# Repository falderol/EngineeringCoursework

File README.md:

This repository contains completed engineering related projects that have been completed while attending taylor university. 
The current order in which projects were completed is.

ENP 104

ENP 232

ENP 252

More projects are currently being worked on. They will be added upon completion.

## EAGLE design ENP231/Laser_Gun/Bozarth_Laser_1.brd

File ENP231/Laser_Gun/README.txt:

File has 3 boards, 1 is main, mode just contains a switch and trigger just contains a button

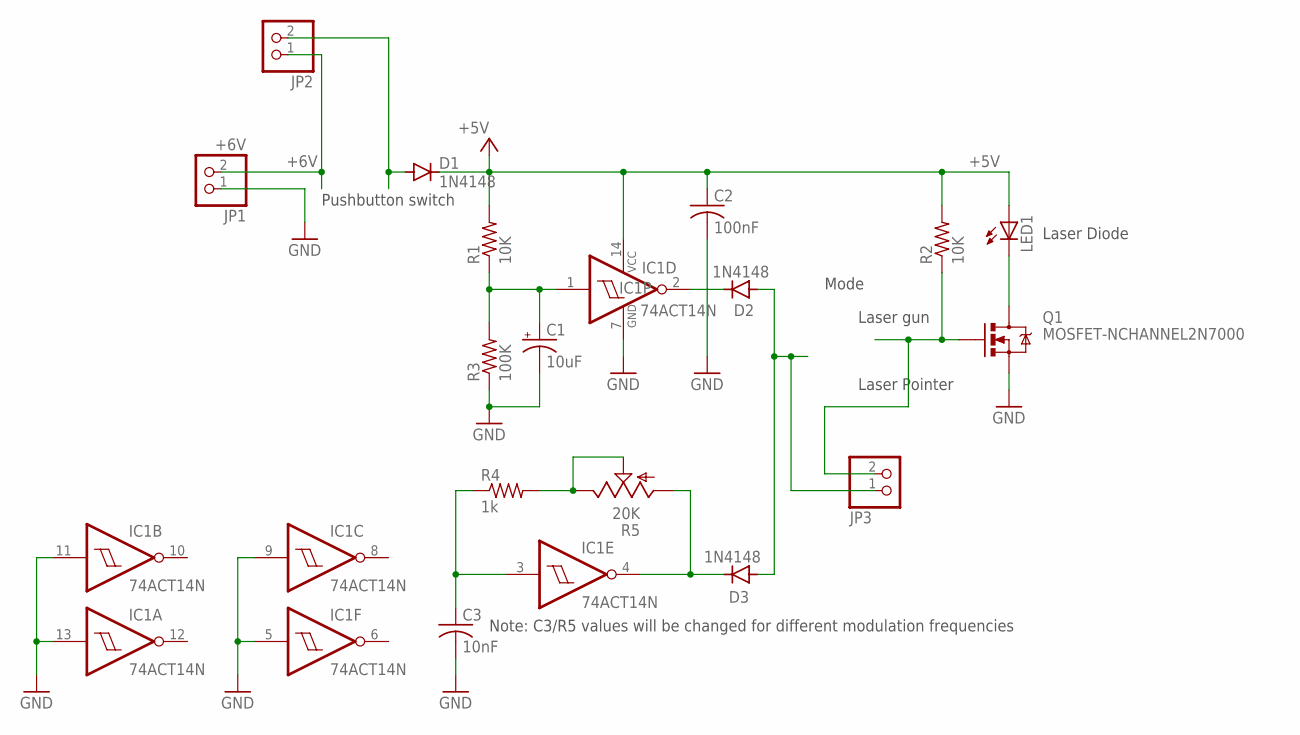
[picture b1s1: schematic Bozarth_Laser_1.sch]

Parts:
C1: 10uF; E2-5
C2: 100nF; C025-025X050
C3: 10nF; C025-025X050
D1, D2, D3: 1N4148; 0207/2V-D
IC1: 74ACT14N; DIL14
JP1: +6V; 1X02
JP2, JP3: PINHD-1X2; 1X02
LED1: LED5MM
Q1: MOSFET-NCHANNEL2N7000; TO-92
R1, R2: 10K; 0207/10
R3: 100K; 0207/10
R4: 1k; 0207/10
R5: 20K; B64Y

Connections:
+5V: C2.1, D1.K (C), IC1.14 (VCC), LED1.A, R1.2, R2.2
+6V: JP1.2, JP2.1
GND: C1.-, C2.2, C3.2, IC1.5 (I), IC1.7 (GND), IC1.9 (I), IC1.11 (I), IC1.13 (I), JP1.1, Q1.1 (S), R3.1
unnamed: C1.+, IC1.1 (I), R1.1, R3.2
unnamed: D2.A, D3.A, JP3.1
unnamed: LED1.K (C), Q1.3 (D)
unnamed: D1.A, JP2.2
unnamed: D2.K (C), IC1.2 (O)
unnamed: D3.K (C), IC1.4 (O), R5.A
unnamed: R4.2, R5.E, R5.S
unnamed: C3.1, IC1.3 (I), R4.1
unnamed: JP3.2, Q1.2 (G), R2.1

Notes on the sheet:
Pushbutton switch
Laser Pointer
Laser gun
Mode
Laser Diode
Note: C3/R5 values will be changed for different modulation frequencies

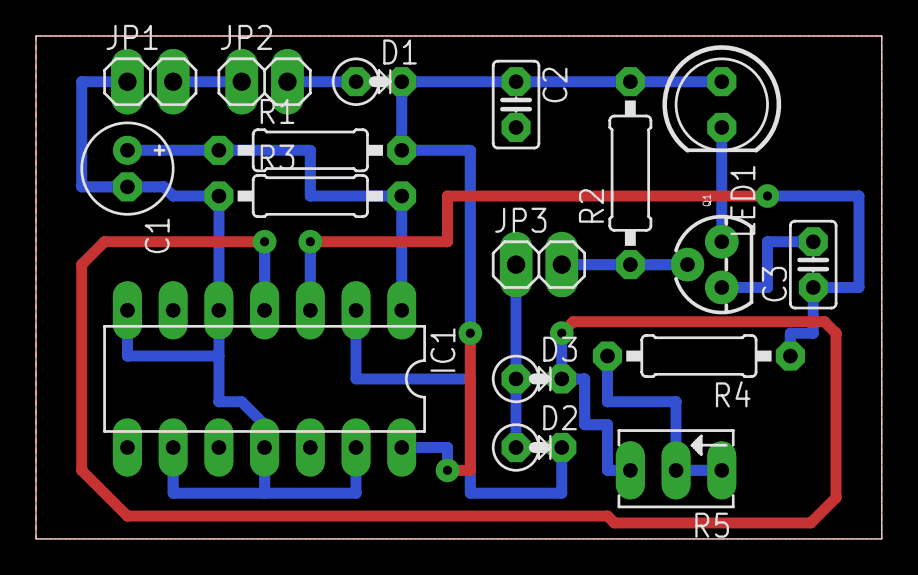
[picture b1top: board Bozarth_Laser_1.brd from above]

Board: 2 copper layers, 47.0 x 27.9 mm, 17 parts (0 on the bottom side), 12 nets.

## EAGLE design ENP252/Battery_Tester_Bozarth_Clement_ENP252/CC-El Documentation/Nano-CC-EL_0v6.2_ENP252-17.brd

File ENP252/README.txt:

Relevant coursework from ENP252 Principles of Engineering. Files included mainly relate to the construction of a programmable ellectronic current load with the class ran through an arduino. And the personal project of developing a battery tester application for said current load.

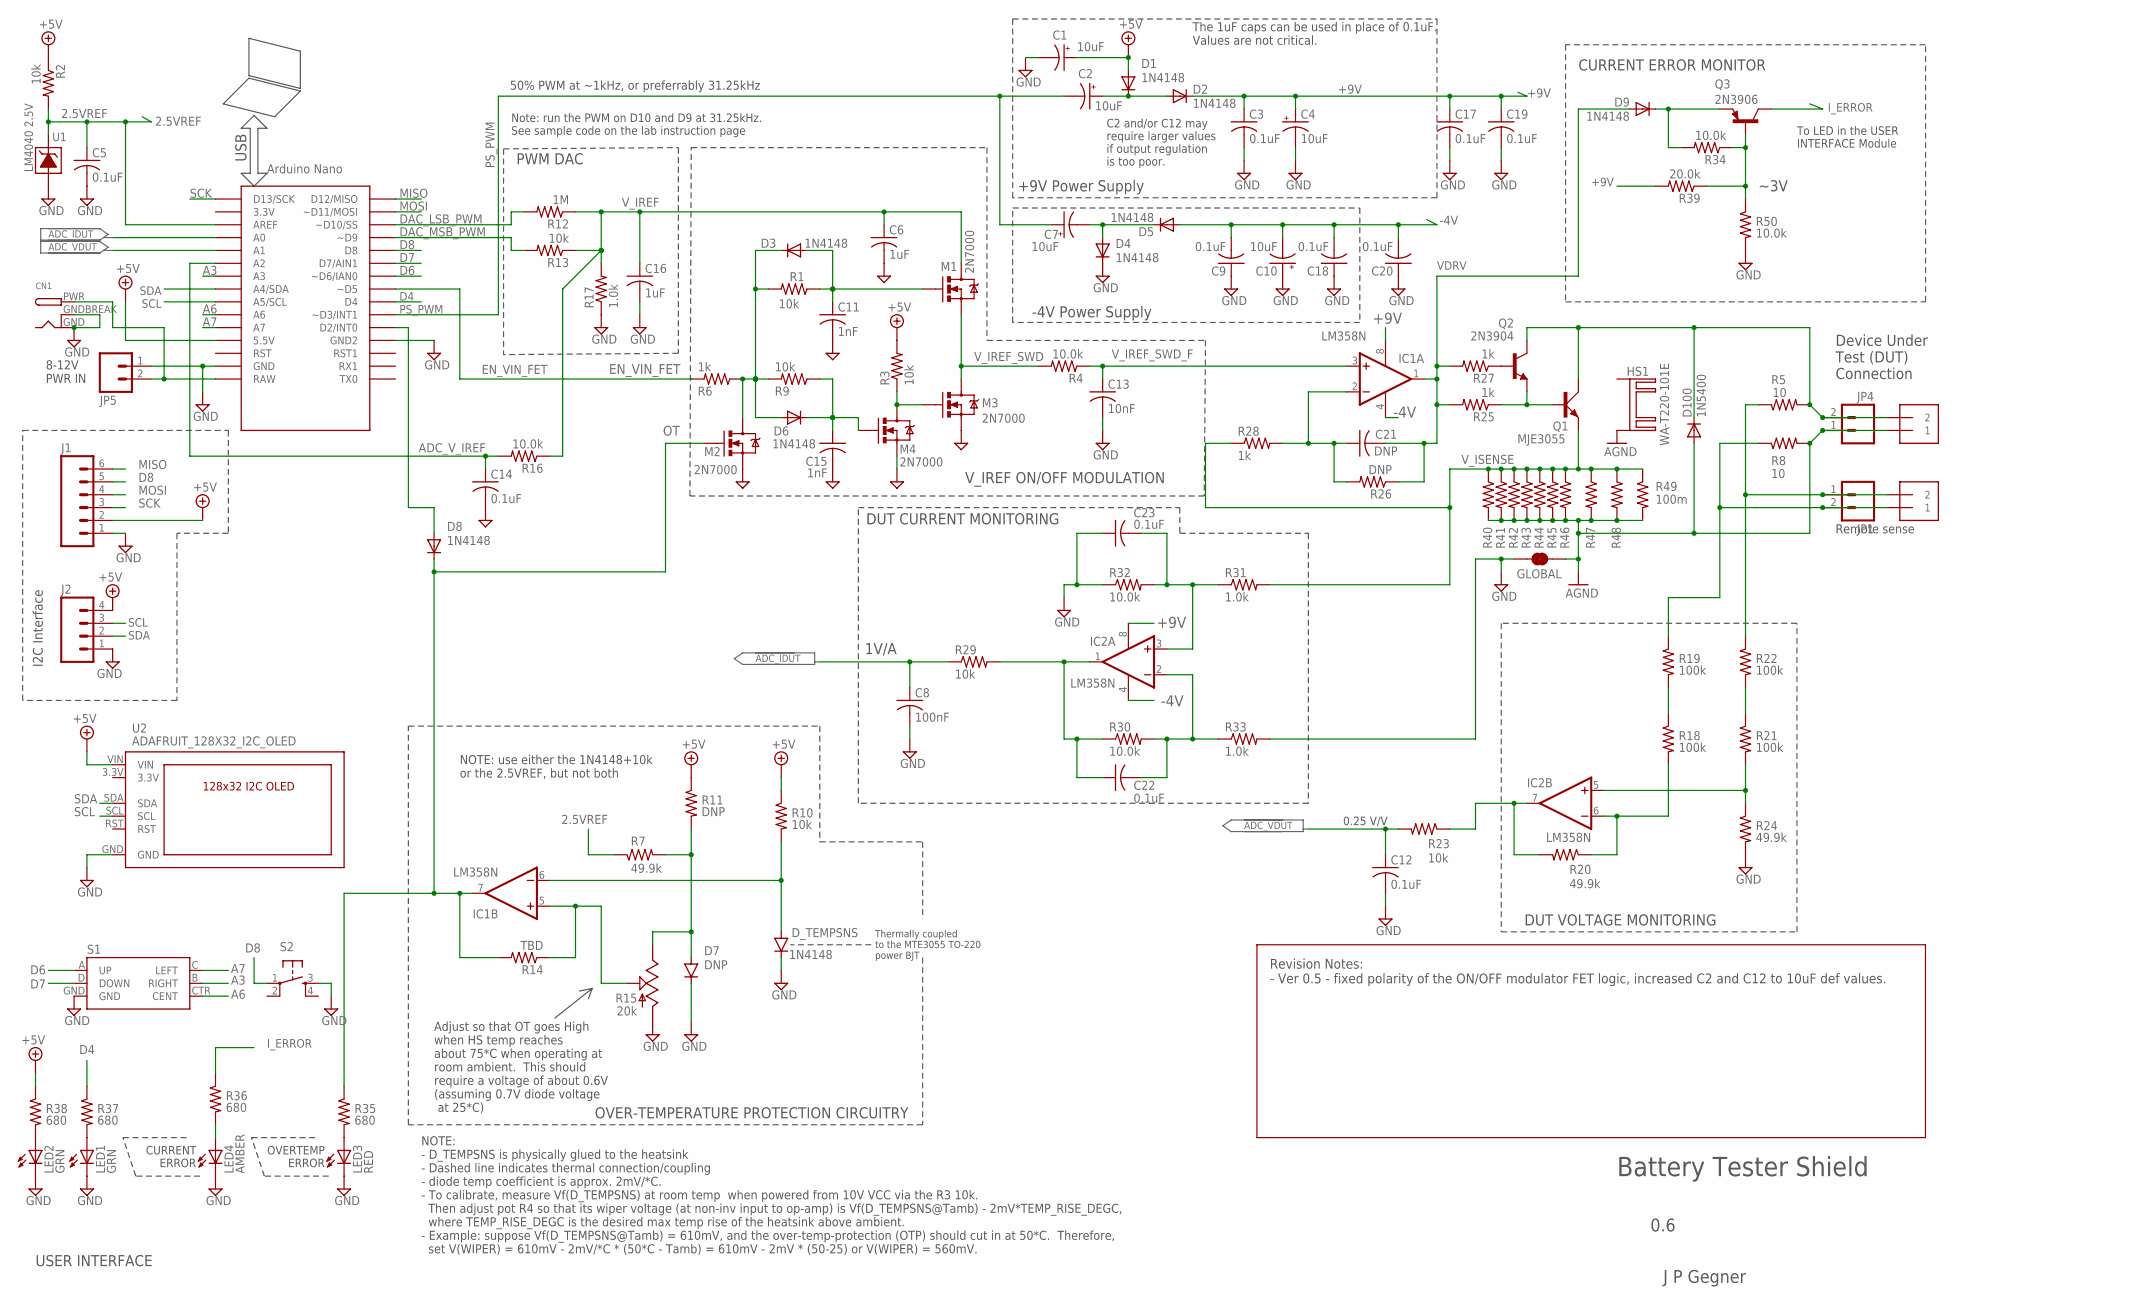
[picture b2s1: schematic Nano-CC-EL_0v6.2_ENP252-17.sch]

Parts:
C1, C2, C4, C7, C10: 10uF; E5-5
C3, C5, C9, C12, C14, C17, C18, C19, C20, C22, C23: 0.1uF; C025-025X050
C6, C16: 1uF; C025-025X050
C8: 100nF; C025-024X044
C11, C15: 1nF; C025-025X050
C13: 10nF; C025-025X050
C21: DNP; C025-025X050
CN1: DCBARRELPTH; DCJACK_2MM_PTH
D1, D2, D3, D4, D5, D6, D8, D9: 1N4148; 0207/2V-D
D7: DNP; 0207/2V-D
D100: 1N5400; DO201-15
D_TEMPSNS: 1N4148; 0207/2V-D
GLOBAL: JUMPER-PAD-2-NC_BY_TRACENO_SILK; PAD-JUMPER-2-NC_BY_TRACE_NO_SILK
HS1: WA-T220-101E; WX-T220-101E
IC1, IC2: LM358N; DIL08
J1: M06POLAR; MOLEX-1X6
J2: M04LOCK_LONGPADS; 1X04_LOCK_LONGPADS
JP1, JP4, JP5: M02PTH; 1X02
JP2, JP3: 1X2-3.5MM
LED1, LED2: GRN; LED3MM-NS
LED3: RED; LED3MM-NS
LED4: AMBER; LED3MM-NS
M1, M2, M3, M4: 2N7000; TO-92
Q1: MJE3055; TO220AV
Q2: 2N3904; TO92
Q3: 2N3906; TO92
R1, R2, R3, R9, R10, R13, R23, R29: 10k; 0204/7
R4, R30: 10.0k; 0204V
R5, R8: 10; 0204V
R6: 1k; 0204V
R7, R24: 49.9k; 0204/7
R11: DNP; 0204/7
R12: 1M; 0204/7
R14: TBD; 0204/7
R15: 20k; B64Y
R16, R32, R34, R50: 10.0k; 0204/7
R17, R31, R33: 1.0k; 0204/7
R18, R19, R21, R22: 100k; 0204/7
R20: 49.9k; 0204V
R25, R27, R28: 1k; 0204/7
R26: DNP; 0204V
R35, R36, R38: 680; 0204/7
R37: 680; 0207/15
R39: 20.0k; 0204/7
R40, R41, R42, R43, R44, R45, R46, R47, R48, R49: 100m; 0204/7
S1: JOYSTICK_MINI
S2: E-SWITCH_TL1105L-F250-Q; OMRON_B3F-1XX-JPGMOD
U1: LM4040 2.5V; TO92
U2: ADAFRUIT_128X32_I2C_OLED
U$1: NANO

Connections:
2.5VREF: C5.1, R2.2, R7.1, U1.2 (CATHODE), U$1.AREF
3.3V: U2.3.3V
+5V: C1.+, D1.A, J1.2, J2.4, R2.1, R3.2, R10.1, R11.1, R38.1, U2.VIN, U$1.5V (5.5V)
+9V: C3.1, C4.+, C17.1, C19.1, D2.K (C), IC1.8 (V+), IC2.8 (V+), R39.2
-4V: C9.2, C10.-, C18.2, C20.2, D5.A, IC1.4 (V-), IC2.4 (V-)
A3: S1.B (RIGHT), U$1.A3
A6: S1.CTR (CENT), U$1.A6
A7: S1.C (LEFT), U$1.A7
ADC_IDUT: C8.1, R29.1, U$1.A0
ADC_VDUT: C12.1, R23.2, U$1.A1
ADC_V_IREF: C14.1, R16.2, U$1.A2
AGND: D100.A, GLOBAL.2, HS1.K2, JP3.1, JP4.1, R8.2, R40.2, R41.2, R42.2, R43.2, R44.2, R45.2, R46.2, R47.2, R48.2, R49.2
D4: R37.1, U$1.D4
D6: S1.A (UP), U$1.D6 (~D6/IAN0)
D7: S1.D (DOWN), U$1.D7 (D7/AIN1)
D8: J1.5, S2.1, U$1.D8
DAC_LSB_PWM: R12.2, U$1.D10 (~D10/SS)
DAC_MSB_PWM: R13.2, U$1.D9 (~D9)
EN_VIN_FET: R6.2, U$1.D5 (~D5)
EN_VIN_FETX: D3.K (C), D6.A, M2.3 (D), R1.2, R6.1, R9.2
GND: C1.-, C3.2, C4.-, C5.2, C6.2, C8.2, C9.1, C10.+, C11.2, C12.2, C13.2, C14.2, C15.2, C16.2, C17.2, C18.1, C19.2, C20.1, C23.1, CN1.GND, CN1.GNDBREAK, D4.K (C), D7.K (C), D_TEMPSNS.K (C), GLOBAL.1, J1.1, J2.1, JP5.1, LED1.K (C), LED2.K (C), LED3.K (C), LED4.K (C), M2.1 (S), M3.1 (S), M4.1 (S), R15.A, R17.1, R24.2, R32.1, R33.2, R50.2, S1.GND, S2.3 (S), U1.3 (ANODE), U2.GND, U$1.GND, U$1.GND1 (GND2)
I_ERROR: Q3.1 (C), R36.1
MISO: J1.6, U$1.D12 (D12/MISO)
MOSI: J1.4, U$1.D11 (~D11/MOSI)
unnamed: D7.A, R7.2, R11.2, R15.E
unnamed: R21.1, R22.2
unnamed: C23.2, IC2.3 (+IN), R31.1, R32.2
unnamed: C22.2, IC2.2 (-IN), R30.2, R33.1
unnamed: D_TEMPSNS.A, IC1.6 (-IN), R10.2
unnamed: IC1.5 (+IN), R14.1, R15.S
unnamed: C11.1, D3.A, M1.2 (G), R1.1
unnamed: D9.K (C), Q3.3 (E), R34.2
unnamed: IC2.6 (-IN), R18.2, R20.1
unnamed: C7.-, D4.A, D5.K (C)
unnamed: LED3.A, R35.2
unnamed: LED2.A, R38.2
unnamed: LED1.A, R37.2
unnamed: C22.1, IC2.1 (OUT), R29.2, R30.1
unnamed: LED4.A, R36.2
unnamed: Q3.2 (B), R34.1, R39.1, R50.1
unnamed: C2.+, D1.K (C), D2.A
unnamed: IC2.5 (+IN), R21.2, R24.1
unnamed: C15.1, D6.K (C), M4.2 (G), R9.1
unnamed: M3.2 (G), M4.3 (D), R3.1
unnamed: JP1.1, JP2.2, R5.1, R22.1
unnamed: D8.A, U$1.D2 (D2/INT0)
unnamed: Q2.2 (B), R27.1
unnamed: D100.C, JP3.2, JP4.2, Q1.C, Q2.1 (C), R5.2
unnamed: Q1.B, Q2.3 (E), R25.1
unnamed: R18.1, R19.2
unnamed: C21.1, IC1.2 (-IN), R26.2, R28.2
unnamed: JP1.2, JP2.1, R8.1, R19.1
OT: D8.K (C), IC1.7 (OUT), M2.2 (G), R14.2, R35.1
PS_PWM: C2.-, C7.+, U$1.D3 (~D3/INT1)
RAW: CN1.PWR, JP5.2, U$1.RAW
SCK: J1.3, U$1.D13 (D13/SCK)
SCL: J2.3, U2.SCL, U$1.A5 (A5/SCL)
SDA: J2.2, U2.SDA, U$1.A4 (A4/SDA)
VDRV: C21.2, D9.A, IC1.1 (OUT), R25.2, R26.1, R27.2
VDUT_OP: IC2.7 (OUT), R20.2, R23.1
V_IREF: C6.1, C16.1, M1.3 (D), R12.1, R13.1, R16.1, R17.2
V_IREF_SWD: M1.1 (S), M3.3 (D), R4.2
V_IREF_SWD_F: C13.1, IC1.3 (+IN), R4.1
V_ISENSE: Q1.E, R28.1, R31.2, R40.1, R41.1, R42.1, R43.1, R44.1, R45.1, R46.1, R47.1, R48.1, R49.1

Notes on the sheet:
Battery Tester Shield
0.6
J P Gegner
NOTE: - D_TEMPSNS is physically glued to the heatsink - Dashed line indicates thermal connection/coupling - diode temp coefficient is approx. 2mV/*C. - To calibrate, measure Vf(D_TEMPSNS) at room temp when powered from 10V VCC via the R3 10k. Then adjust pot R4 so that its wiper voltage (at non-inv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
Adjust so that OT goes High when HS temp reaches about 75*C when operating at room ambient. This should require a voltage of about 0.6V (assuming 0.7V diode voltage at 25*C)
OVER-TEMPERATURE PROTECTION CIRCUITRY
Thermally coupled to the MTE3055 TO-220 power BJT
The 1uF caps can be used in place of 0.1uF. Values are not critical.
8-12V PWR IN
50% PWM at ~1kHz, or preferrably 31.25kHz
+9V Power Supply
-4V Power Supply
Device Under Test (DUT) Connection
PWM DAC
V_IREF ON/OFF MODULATION
DUT CURRENT MONITORING
DUT VOLTAGE MONITORING
USER INTERFACE
USB
1V/A
Note: run the PWM on D10 and D9 at 31.25kHz. See sample code on the lab instruction page
0.25 V/V
CURRENT ERROR
OVERTEMP ERROR
To LED in the USER INTERFACE Module
CURRENT ERROR MONITOR
~3V
I2C Interface
C2 and/or C12 may require larger values if output regulation is too poor.
Revision Notes: - Ver 0.5 - fixed polarity of the ON/OFF modulator FET logic, increased C2 and C12 to 10uF def values.
Remote sense
NOTE: use either the 1N4148+10k or the 2.5VREF, but not both

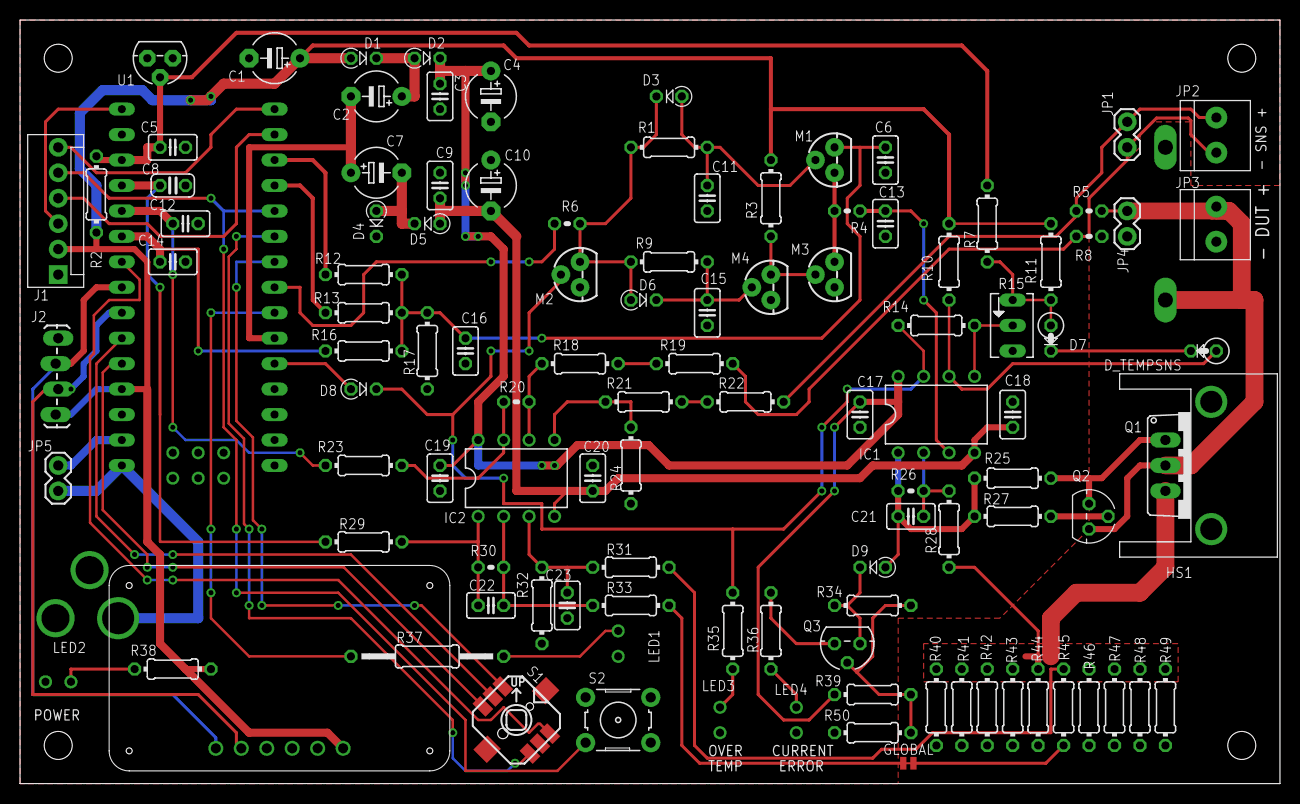
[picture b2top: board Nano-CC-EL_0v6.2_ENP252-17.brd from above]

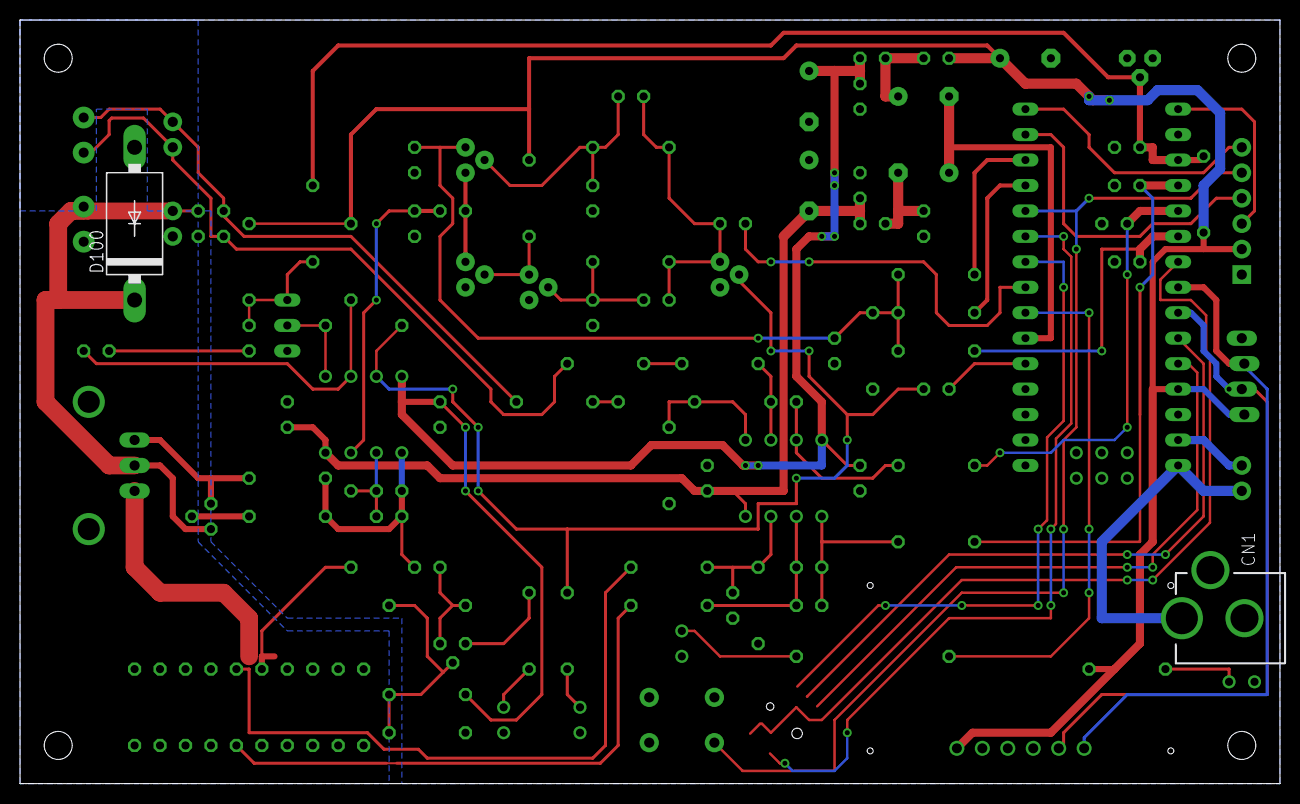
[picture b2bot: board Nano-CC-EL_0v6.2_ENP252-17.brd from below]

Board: 2 copper layers, 125.7 x 76.2 mm, 112 parts (2 on the bottom side), 63 nets.

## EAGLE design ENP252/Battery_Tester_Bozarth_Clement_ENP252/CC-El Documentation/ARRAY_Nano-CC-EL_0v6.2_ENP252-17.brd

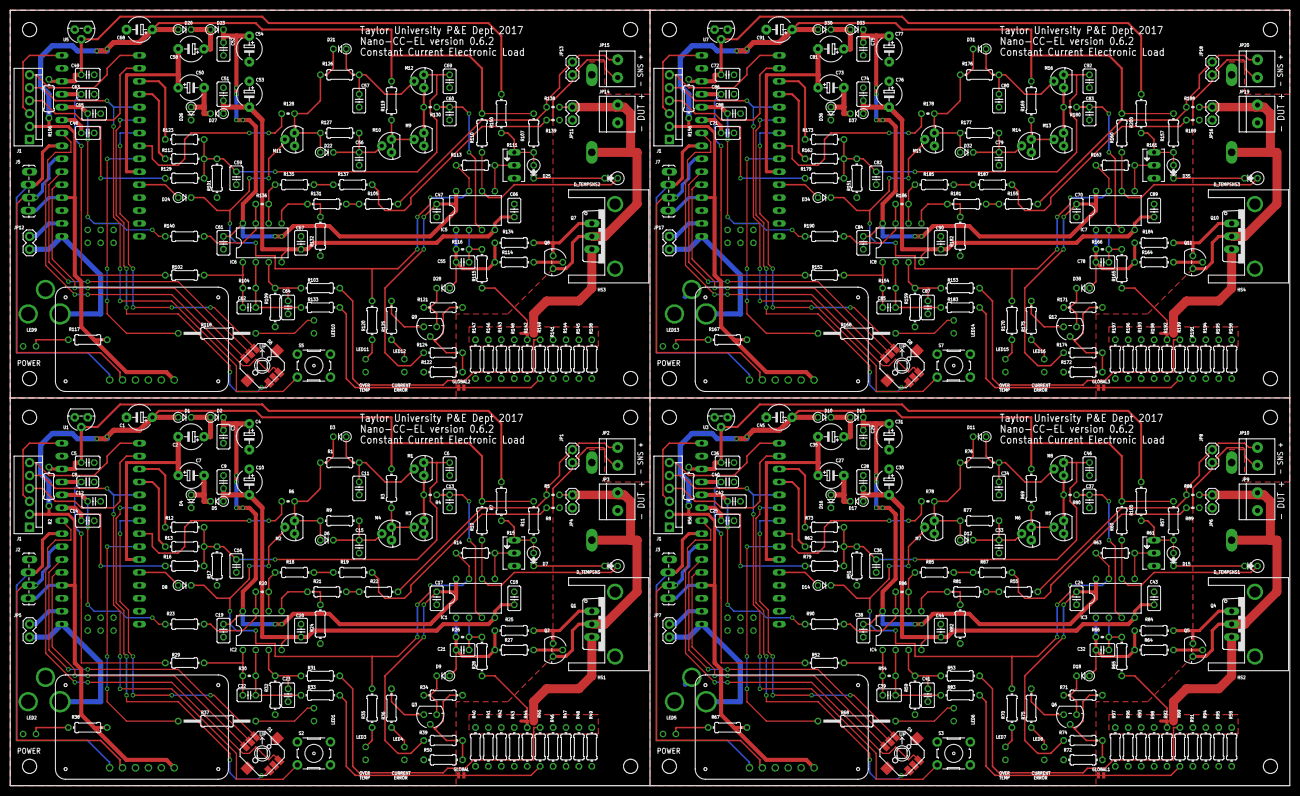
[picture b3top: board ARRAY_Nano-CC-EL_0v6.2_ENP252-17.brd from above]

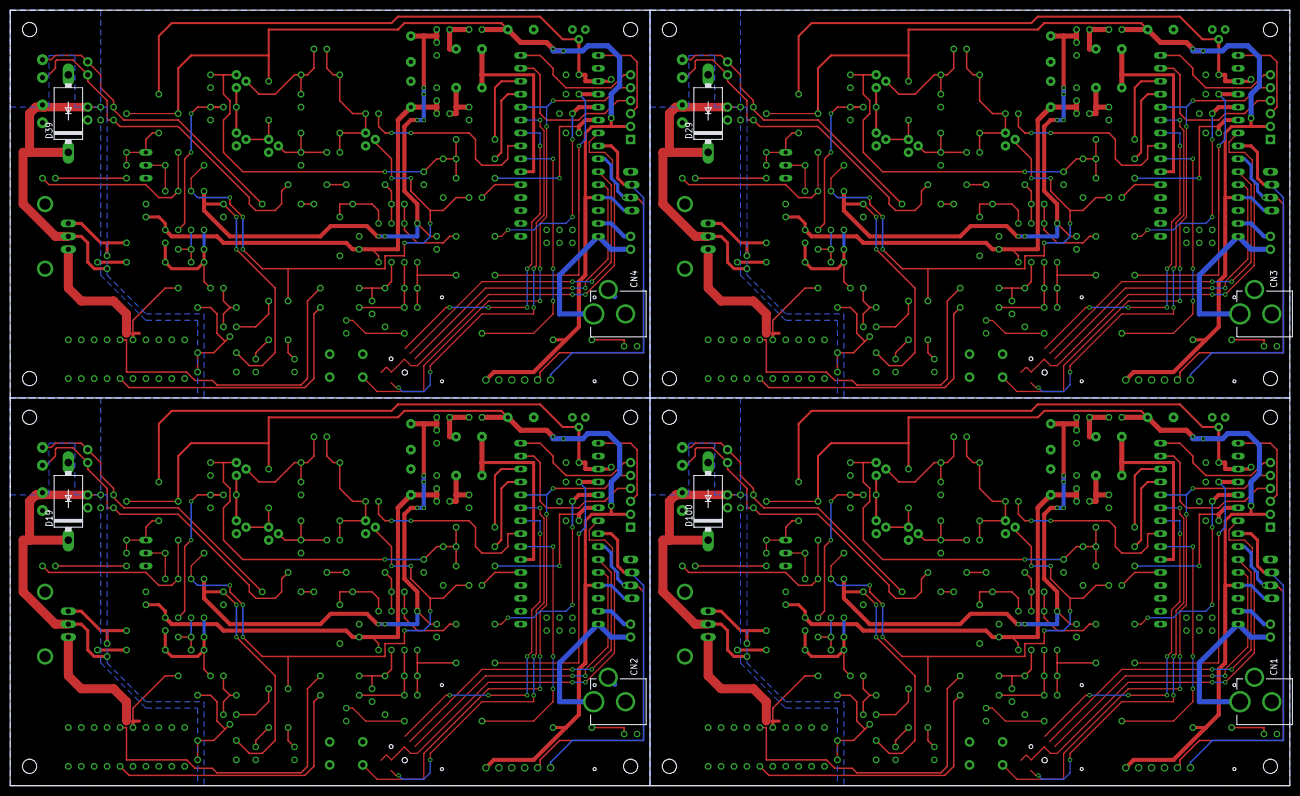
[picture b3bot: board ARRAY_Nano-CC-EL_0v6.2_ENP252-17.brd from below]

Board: 2 copper layers, 251.5 x 152.4 mm, 448 parts (8 on the bottom side), 252 nets.

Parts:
C1, C2, C4, C7, C10, C27, C30, C31, C35, C45, C50, C53, C54, C58, C68, C73, C76, C77, C81, C91: 10uF; E5-5
C3, C6, C9, C12, C17, C18, C19, C20, C22, C23, C24, C28, C29, C38, C39, C41, C42, C43, C44, C46, C47, C51, C52, C61, C62, C64, C65, C66, C67, C69, C70, C74, C75, C84, C85, C87, C88, C89, C90, C92: 0.1uF; C025-025X050
C5, C26, C49, C72: 0.1u; C025-025X050
C8, C40, C63, C86: 100nF; C025-024X044
C11, C15, C33, C34, C56, C57, C79, C80: 1nF; C025-025X050
C13, C14, C16, C21, C25, C32, C36, C37, C48, C55, C59, C60, C71, C78, C82, C83: TBD; C025-025X050
CN1, CN2, CN3, CN4: DCJACK_2MM_PTH
D1, D2, D3, D4, D5, D6, D7, D8, D9, D10, D11, D12, D13, D14, D15, D16, D17, D18, D20, D21, D22, D23, D24, D25, D26, D27, D28, D30, D31, D32, D33, D34, D35, D36, D37, D38: 1N4148; 0207/2V-D
D19, D29, D39, D100: 1N5400; DO201-15
D_TEMPSNS, D_TEMPSNS1, D_TEMPSNS2, D_TEMPSNS3: 1N4148; 0207/2V-D
GLOBAL, GLOBAL1, GLOBAL2, GLOBAL3: PAD-JUMPER-2-NC_BY_TRACE_NO_SILK
HS1, HS2, HS3, HS4: WA-T220-101E; WX-T220-101E
IC1, IC2, IC3, IC4, IC5, IC6, IC7, IC8: LM358N; DIL08
J1, J4, J6, J8: MOLEX-1X6
J2, J3, J5, J7: 1X04_LOCK_LONGPADS
JP1, JP4, JP5, JP6, JP7, JP8, JP11, JP12, JP13, JP16, JP17, JP18: 1X02
JP2, JP3, JP9, JP10, JP14, JP15, JP19, JP20: 1X2-3.5MM
LED1, LED2, LED3, LED4, LED5, LED6, LED7, LED8, LED9, LED10, LED11, LED12, LED13, LED14, LED15, LED16: LED3MM-NS
M1, M2, M3, M4, M5, M6, M7, M8, M9, M10, M11, M12, M13, M14, M15, M16: 2N7000; TO-92
Q1, Q4, Q7, Q10: MJE3055; TO220AV
Q2, Q5, Q8, Q11: 2N3904; TO92
Q3, Q6, Q9, Q12: 2N3906; TO92
R1, R3, R7, R9, R10, R11, R23, R29, R52, R57, R60, R69, R76, R77, R90, R100, R102, R107, R110, R119, R126, R127, R140, R150, R152, R157, R160, R169, R176, R177, R190, R200: 10k; 0204/7
R2, R56, R106, R156: 20k; 0204/7
R4, R26, R66, R80, R116, R130, R166, R180: TBD; 0204V
R5, R8, R88, R89, R138, R139, R188, R189: 10; 0204V
R6, R78, R128, R178: 1k; 0204V
R12, R13, R14, R16, R17, R28, R51, R62, R63, R65, R73, R79, R101, R112, R113, R115, R123, R129, R151, R162, R163, R165, R173, R179: TBD; 0204/7
R15, R61, R111, R161: 10-50k; B64Y
R18, R19, R21, R22, R55, R81, R85, R87, R105, R131, R135, R137, R155, R181, R185, R187: 100k; 0204/7
R20, R86, R136, R186: 49.9k; 0204V
R24, R82, R132, R182: 49.9k; 0204/7
R25, R27, R64, R84, R114, R134, R164, R184: 1k; 0204/7
R30, R54, R104, R154: 10.0k; 0204V
R31, R33, R53, R83, R103, R133, R153, R183: 1.0k; 0204/7
R32, R34, R50, R59, R71, R72, R109, R121, R122, R159, R171, R172: 10.0k; 0204/7
R35, R36, R38, R67, R70, R75, R117, R120, R125, R167, R170, R175: 680; 0204/7
R37, R68, R118, R168: 680; 0207/15
R39, R74, R124, R174: 20.0k; 0204/7
R40, R41, R42, R43, R44, R45, R46, R47, R48, R49, R58, R91, R92, R93, R94, R95, R96, R97, R98, R99, R108, R141, R142, R143, R144, R145, R146, R147, R148, R149, R158, R191, R192, R193, R194, R195, R196, R197, R198, R199: 100m; 0204/7
S1, S4, S6, S8: JOYSTICK_MINI
S2, S3, S5, S7: OMRON_B3F-1XX-JPGMOD
U1, U3, U5, U7: LM4040 2.5V; TO92
U2, U4, U6, U8: ADAFRUIT_128X32_I2C_OLED
U$1, U$2, U$3, U$4: NANO

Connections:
2.5VREF: C5.1, R2.2, R7.1, U1.2, U$1.AREF
2.5VREF1: C26.1, R56.2, R100.1, U3.2, U$2.AREF
2.5VREF2: C49.1, R106.2, R150.1, U5.2, U$3.AREF
2.5VREF3: C72.1, R156.2, R200.1, U7.2, U$4.AREF
+5V: C1.+, D1.A, J1.2, J2.4, R2.1, R3.2, R10.1, R11.1, R38.1, U2.VIN, U$1.5V
+5V1: C45.+, D10.A, J3.4, J4.2, R56.1, R57.1, R60.1, R67.1, R69.2, U4.VIN, U$2.5V
+5V2: C68.+, D20.A, J5.4, J6.2, R106.1, R107.1, R110.1, R117.1, R119.2, U6.VIN, U$3.5V
+5V3: C91.+, D30.A, J7.4, J8.2, R156.1, R157.1, R160.1, R167.1, R169.2, U8.VIN, U$4.5V
+9V: C3.1, C4.+, C17.1, C19.1, D2.K, IC1.8, IC2.8, R39.2
+9V1: C24.1, C29.1, C31.+, C38.1, D13.K, IC3.8, IC4.8, R74.2
+9V2: C47.1, C52.1, C54.+, C61.1, D23.K, IC5.8, IC6.8, R124.2
+9V3: C70.1, C75.1, C77.+, C84.1, D33.K, IC7.8, IC8.8, R174.2
-4V: C9.2, C10.-, C18.2, C20.2, D5.A, IC1.4, IC2.4
-4V1: C28.2, C30.-, C43.2, C44.2, D17.A, IC3.4, IC4.4
-4V2: C51.2, C53.-, C66.2, C67.2, D27.A, IC5.4, IC6.4
-4V3: C74.2, C76.-, C89.2, C90.2, D37.A, IC7.4, IC8.4
A1: S4.B, U$2.A3
A2: S4.CTR, U$2.A6
A3: S1.B, U$1.A3
A4: S4.C, U$2.A7
A5: S6.B, U$3.A3
A6: S1.CTR, U$1.A6
A7: S1.C, U$1.A7
A8: S6.CTR, U$3.A6
A9: S6.C, U$3.A7
A10: S8.B, U$4.A3
A11: S8.CTR, U$4.A6
A12: S8.C, U$4.A7
ADC_IDUT: C8.1, R29.1, U$1.A0
ADC_IDUT1: C40.1, R52.1, U$2.A0
ADC_IDUT2: C63.1, R102.1, U$3.A0
ADC_IDUT3: C86.1, R152.1, U$4.A0
ADC_VDUT: C12.1, R23.2, U$1.A1
ADC_VDUT1: C42.1, R90.2, U$2.A1
ADC_VDUT2: C65.1, R140.2, U$3.A1
ADC_VDUT3: C88.1, R190.2, U$4.A1
ADC_V_IREF: C14.1, R16.2, U$1.A2
ADC_V_IREF1: C25.1, R79.2, U$2.A2
ADC_V_IREF2: C48.1, R129.2, U$3.A2
ADC_V_IREF3: C71.1, R179.2, U$4.A2
AGND: D100.A, GLOBAL.2, HS1.K2, JP3.1, JP4.1, R8.2, R40.2, R41.2, R42.2, R43.2, R44.2, R45.2, R46.2, R47.2, R48.2, R49.2
AGND1: D19.A, GLOBAL1.2, HS2.K2, JP6.1, JP9.1, R58.2, R89.2, R91.2, R92.2, R93.2, R94.2, R95.2, R96.2, R97.2, R98.2, R99.2
AGND2: D29.A, GLOBAL2.2, HS3.K2, JP11.1, JP14.1, R108.2, R139.2, R141.2, R142.2, R143.2, R144.2, R145.2, R146.2, R147.2, R148.2, R149.2
AGND3: D39.A, GLOBAL3.2, HS4.K2, JP16.1, JP19.1, R158.2, R189.2, R191.2, R192.2, R193.2, R194.2, R195.2, R196.2, R197.2, R198.2, R199.2
D1: R68.1, U$2.D4
D2: S4.A, U$2.D6
D3: J4.5, S3.1, U$2.D8
D4: R37.1, U$1.D4
D5: S4.D, U$2.D7
D6: S1.A, U$1.D6
D7: S1.D, U$1.D7
D8: J1.5, S2.1, U$1.D8
D9: R118.1, U$3.D4
D10: S6.A, U$3.D6
D11: J6.5, S5.1, U$3.D8
D12: S6.D, U$3.D7
D13: R168.1, U$4.D4
D14: S8.A, U$4.D6
D15: J8.5, S7.1, U$4.D8
D16: S8.D, U$4.D7
DAC_LSB_PWM: R12.2, U$1.D10
DAC_LSB_PWM1: R73.2, U$2.D10
DAC_LSB_PWM2: R123.2, U$3.D10
DAC_LSB_PWM3: R173.2, U$4.D10
DAC_MSB_PWM: R13.2, U$1.D9
DAC_MSB_PWM1: R62.2, U$2.D9
DAC_MSB_PWM2: R112.2, U$3.D9
DAC_MSB_PWM3: R162.2, U$4.D9
EN_VIN_FET: R6.2, U$1.D5
EN_VIN_FET1: R78.2, U$2.D5
EN_VIN_FET2: R128.2, U$3.D5
EN_VIN_FET3: R178.2, U$4.D5
EN_VIN_FETX: D3.K, D6.A, M2.3, R1.2, R6.1, R9.2
EN_VIN_FETX1: D11.K, D12.A, M7.3, R76.2, R77.2, R78.1
EN_VIN_FETX2: D21.K, D22.A, M11.3, R126.2, R127.2, R128.1
EN_VIN_FETX3: D31.K, D32.A, M15.3, R176.2, R177.2, R178.1
GND: C1.-, C3.2, C4.-, C5.2, C6.2, C8.2, C9.1, C10.+, C11.2, C12.2, C13.2, C14.2, C15.2, C16.2, C17.2, C18.1, C19.2, C20.1, C23.1, CN1.GND, CN1.GNDBREAK, D4.K, D7.K, D_TEMPSNS.K, GLOBAL.1, J1.1, J2.1, JP5.1, LED1.K, LED2.K, LED3.K, LED4.K, M2.1, M3.1, M4.1, R15.A, R17.1, R24.2, R32.1, R33.2, R50.2, S1.GND, S2.3, U1.3, U2.GND, U$1.GND, U$1.GND1
GND1: C24.2, C25.2, C26.2, C28.1, C29.2, C30.+, C31.-, C33.2, C34.2, C36.2, C37.2, C38.2, C40.2, C41.1, C42.2, C43.1, C44.1, C45.-, C46.2, CN2.GND, CN2.GNDBREAK, D15.K, D16.K, D_TEMPSNS1.K, GLOBAL1.1, J3.1, J4.1, JP7.1, LED5.K, LED6.K, LED7.K, LED8.K, M5.1, M6.1, M7.1, R51.1, R59.1, R61.A, R72.2, R82.2, R83.2, S3.3, S4.GND, U3.3, U4.GND, U$2.GND, U$2.GND1
GND2: C47.2, C48.2, C49.2, C51.1, C52.2, C53.+, C54.-, C56.2, C57.2, C59.2, C60.2, C61.2, C63.2, C64.1, C65.2, C66.1, C67.1, C68.-, C69.2, CN3.GND, CN3.GNDBREAK, D25.K, D26.K, D_TEMPSNS2.K, GLOBAL2.1, J5.1, J6.1, JP12.1, LED9.K, LED10.K, LED11.K, LED12.K, M9.1, M10.1, M11.1, R101.1, R109.1, R111.A, R122.2, R132.2, R133.2, S5.3, S6.GND, U5.3, U6.GND, U$3.GND, U$3.GND1
GND3: C70.2, C71.2, C72.2, C74.1, C75.2, C76.+, C77.-, C79.2, C80.2, C82.2, C83.2, C84.2, C86.2, C87.1, C88.2, C89.1, C90.1, C91.-, C92.2, CN4.GND, CN4.GNDBREAK, D35.K, D36.K, D_TEMPSNS3.K, GLOBAL3.1, J7.1, J8.1, JP17.1, LED13.K, LED14.K, LED15.K, LED16.K, M13.1, M14.1, M15.1, R151.1, R159.1, R161.A, R172.2, R182.2, R183.2, S7.3, S8.GND, U7.3, U8.GND, U$4.GND, U$4.GND1
I_ERROR: Q3.1, R36.1
I_ERROR1: Q6.1, R75.1
I_ERROR2: Q9.1, R125.1
I_ERROR3: Q12.1, R175.1
MISO: J1.6, U$1.D12
MISO1: J4.6, U$2.D12
MISO2: J6.6, U$3.D12
MISO3: J8.6, U$4.D12
MOSI: J1.4, U$1.D11
MOSI1: J4.4, U$2.D11
MOSI2: J6.4, U$3.D11
MOSI3: J8.4, U$4.D11
unnamed: D7.A, R7.2, R11.2, R15.E
unnamed: R21.1, R22.2
unnamed: C23.2, IC2.3, R31.1, R32.2
unnamed: C22.2, IC2.2, R30.2, R33.1
unnamed: D_TEMPSNS.A, IC1.6, R10.2
unnamed: IC1.5, R14.1, R15.S
unnamed: C35.+, D10.K, D13.A
unnamed: C11.1, D3.A, M1.2, R1.1
unnamed: D9.K, Q3.3, R34.2
unnamed: IC2.6, R18.2, R20.1
unnamed: C7.-, D4.A, D5.K
unnamed: LED3.A, R35.2
unnamed: LED2.A, R38.2
unnamed: LED1.A, R37.2
unnamed: C22.1, IC2.1, R29.2, R30.1
unnamed: LED4.A, R36.2
unnamed: Q3.2, R34.1, R39.1, R50.1
unnamed: C2.+, D1.K, D2.A
unnamed: IC2.5, R21.2, R24.1
unnamed: C15.1, D6.K, M4.2, R9.1
unnamed: M3.2, M4.3, R3.1
unnamed: JP1.1, JP2.2, R5.1, R22.1
unnamed: D8.A, U$1.D2
unnamed: Q2.2, R27.1
unnamed: D100.C, JP3.2, JP4.2, Q1.C, Q2.1, R5.2
unnamed: Q1.B, Q2.3, R25.1
unnamed: R18.1, R19.2
unnamed: C21.1, IC1.2, R26.2, R28.2
unnamed: JP1.2, JP2.1, R8.1, R19.1
unnamed: D19.C, JP6.2, JP9.2, Q4.C, Q5.1, R88.2
unnamed: C27.-, D16.A, D17.K
unnamed: C41.2, IC4.3, R53.1, R59.2
unnamed: C39.2, IC4.2, R54.2, R83.1
unnamed: C39.1, IC4.1, R52.2, R54.1
unnamed: D15.A, R57.2, R61.E, R100.2
unnamed: D_TEMPSNS1.A, IC3.6, R60.2
unnamed: IC3.5, R61.S, R63.1
unnamed: Q5.2, R64.1
unnamed: Q4.B, Q5.3, R84.1
unnamed: C32.1, IC3.2, R65.2, R66.2
unnamed: D14.A, U$2.D2
unnamed: LED5.A, R67.2
unnamed: LED6.A, R68.2
unnamed: R55.2, R81.1
unnamed: LED7.A, R70.2
unnamed: D18.K, Q6.3, R71.2
unnamed: Q6.2, R71.1, R72.1, R74.1
unnamed: LED8.A, R75.2
unnamed: C33.1, D12.K, M6.2, R77.1
unnamed: C34.1, D11.A, M8.2, R76.1
unnamed: M5.2, M6.3, R69.1
unnamed: IC4.5, R81.2, R82.1
unnamed: R85.1, R87.2
unnamed: IC4.6, R85.2, R86.1
unnamed: JP8.1, JP10.2, R55.1, R88.1
unnamed: JP8.2, JP10.1, R87.1, R89.1
unnamed: C58.+, D20.K, D23.A
unnamed: D29.C, JP11.2, JP14.2, Q7.C, Q8.1, R138.2
unnamed: C50.-, D26.A, D27.K
unnamed: C64.2, IC6.3, R103.1, R109.2
unnamed: C62.2, IC6.2, R104.2, R133.1
unnamed: C62.1, IC6.1, R102.2, R104.1
unnamed: D25.A, R107.2, R111.E, R150.2
unnamed: D_TEMPSNS2.A, IC5.6, R110.2
unnamed: IC5.5, R111.S, R113.1
unnamed: Q8.2, R114.1
unnamed: Q7.B, Q8.3, R134.1
unnamed: C55.1, IC5.2, R115.2, R116.2
unnamed: D24.A, U$3.D2
unnamed: LED9.A, R117.2
unnamed: LED10.A, R118.2
unnamed: R105.2, R131.1
unnamed: LED11.A, R120.2
unnamed: D28.K, Q9.3, R121.2
unnamed: Q9.2, R121.1, R122.1, R124.1
unnamed: LED12.A, R125.2
unnamed: C56.1, D22.K, M10.2, R127.1
unnamed: C57.1, D21.A, M12.2, R126.1
unnamed: M9.2, M10.3, R119.1
unnamed: IC6.5, R131.2, R132.1
unnamed: R135.1, R137.2
unnamed: IC6.6, R135.2, R136.1
unnamed: JP13.1, JP15.2, R105.1, R138.1
unnamed: JP13.2, JP15.1, R137.1, R139.1
unnamed: C81.+, D30.K, D33.A
unnamed: D39.C, JP16.2, JP19.2, Q10.C, Q11.1, R188.2
unnamed: C73.-, D36.A, D37.K
unnamed: C87.2, IC8.3, R153.1, R159.2
unnamed: C85.2, IC8.2, R154.2, R183.1
unnamed: C85.1, IC8.1, R152.2, R154.1
unnamed: D35.A, R157.2, R161.E, R200.2
unnamed: D_TEMPSNS3.A, IC7.6, R160.2
unnamed: IC7.5, R161.S, R163.1
unnamed: Q11.2, R164.1
unnamed: Q10.B, Q11.3, R184.1
unnamed: C78.1, IC7.2, R165.2, R166.2
unnamed: D34.A, U$4.D2
unnamed: LED13.A, R167.2
unnamed: LED14.A, R168.2
unnamed: R155.2, R181.1
unnamed: LED15.A, R170.2
unnamed: D38.K, Q12.3, R171.2
unnamed: Q12.2, R171.1, R172.1, R174.1
unnamed: LED16.A, R175.2
unnamed: C79.1, D32.K, M14.2, R177.1
unnamed: C80.1, D31.A, M16.2, R176.1
unnamed: M13.2, M14.3, R169.1
unnamed: IC8.5, R181.2, R182.1
unnamed: R185.1, R187.2
unnamed: IC8.6, R185.2, R186.1
unnamed: JP18.1, JP20.2, R155.1, R188.1
unnamed: JP18.2, JP20.1, R187.1, R189.1
OT: D8.K, IC1.7, M2.2, R14.2, R35.1
OT1: D14.K, IC3.7, M7.2, R63.2, R70.1
OT2: D24.K, IC5.7, M11.2, R113.2, R120.1
OT3: D34.K, IC7.7, M15.2, R163.2, R170.1
PS_PWM: C2.-, C7.+, U$1.D3
PS_PWM1: C27.+, C35.-, U$2.D3
PS_PWM2: C50.+, C58.-, U$3.D3
PS_PWM3: C73.+, C81.-, U$4.D3
RAW: CN1.PWR, JP5.2, U$1.RAW
RAW1: CN2.PWR, JP7.2, U$2.RAW
RAW2: CN3.PWR, JP12.2, U$3.RAW
RAW3: CN4.PWR, JP17.2, U$4.RAW
SCK: J1.3, U$1.D13
SCK1: J4.3, U$2.D13
SCK2: J6.3, U$3.D13
SCK3: J8.3, U$4.D13
SCL: J2.3, U2.SCL, U$1.A5
SCL1: J3.3, U4.SCL, U$2.A5
SCL2: J5.3, U6.SCL, U$3.A5
SCL3: J7.3, U8.SCL, U$4.A5
SDA: J2.2, U2.SDA, U$1.A4
SDA1: J3.2, U4.SDA, U$2.A4
SDA2: J5.2, U6.SDA, U$3.A4
SDA3: J7.2, U8.SDA, U$4.A4
VDRV: C21.2, D9.A, IC1.1, R25.2, R26.1, R27.2
VDRV1: C32.2, D18.A, IC3.1, R64.2, R66.1, R84.2
VDRV2: C55.2, D28.A, IC5.1, R114.2, R116.1, R134.2
VDRV3: C78.2, D38.A, IC7.1, R164.2, R166.1, R184.2
VDUT_OP: IC2.7, R20.2, R23.1
VDUT_OP1: IC4.7, R86.2, R90.1
VDUT_OP2: IC6.7, R136.2, R140.1
VDUT_OP3: IC8.7, R186.2, R190.1
V_IREF: C6.1, C16.1, M1.3, R12.1, R13.1, R16.1, R17.2
V_IREF1: C36.1, C46.1, M8.3, R51.2, R62.1, R73.1, R79.1
V_IREF2: C59.1, C69.1, M12.3, R101.2, R112.1, R123.1, R129.1
V_IREF3: C82.1, C92.1, M16.3, R151.2, R162.1, R173.1, R179.1
V_IREF_SWD: M1.1, M3.3, R4.2
V_IREF_SWD1: M5.3, M8.1, R80.2
V_IREF_SWD2: M9.3, M12.1, R130.2
V_IREF_SWD3: M13.3, M16.1, R180.2
V_IREF_SWD_F: C13.1, IC1.3, R4.1
V_IREF_SWD_F1: C37.1, IC3.3, R80.1
V_IREF_SWD_F2: C60.1, IC5.3, R130.1
V_IREF_SWD_F3: C83.1, IC7.3, R180.1
V_ISENSE: Q1.E, R28.1, R31.2, R40.1, R41.1, R42.1, R43.1, R44.1, R45.1, R46.1, R47.1, R48.1, R49.1
V_ISENSE1: Q4.E, R53.2, R58.1, R65.1, R91.1, R92.1, R93.1, R94.1, R95.1, R96.1, R97.1, R98.1, R99.1
V_ISENSE2: Q7.E, R103.2, R108.1, R115.1, R141.1, R142.1, R143.1, R144.1, R145.1, R146.1, R147.1, R148.1, R149.1
V_ISENSE3: Q10.E, R153.2, R158.1, R165.1, R191.1, R192.1, R193.1, R194.1, R195.1, R196.1, R197.1, R198.1, R199.1

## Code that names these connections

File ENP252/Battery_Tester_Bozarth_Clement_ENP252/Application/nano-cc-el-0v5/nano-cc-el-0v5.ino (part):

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//// HARDWARE IO DEFINITIONS
#define PIN_DAC_LSB 10
#define PIN_DAC_MSB 9
#define PIN_PS_PWM 3
#define PIN_EN_VIN_FET 5
//
#define PIN_LED_GRN 4
#define PIN_LED_RED_13  13
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#define PIN_SW_RT A3
#define PIN_SW_LT A7

#define PIN_ADC_IDUT  A0
#define PIN_ADC_VDUT  A1
#define PIN_ADC_V_IREF A2
//
// OLED RST PIN. - we actually don't have one...
// wire a 10uF ceramic SMD cap between the RST pinMode
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  // use pin 13 to probe the frequency at which ADC service is running.
  //digitalWrite(PIN_LED_RED_13,HIGH);

  adc_wavg((unsigned int)analogRead(PIN_ADC_V_IREF), &nv_iref);
  adc_wavg((unsigned int)analogRead(PIN_ADC_VDUT), &nv_dut);
  adc_wavg((unsigned int)analogRead(PIN_ADC_IDUT), &ni_dut);

  /* Serial.println("--N*ADC--");
    Serial.println(nv_iref);
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    Serial.println(ni_dut);

    Serial.println("--raw ADC--");
    Serial.println(analogRead(PIN_ADC_V_IREF));
    //Serial.println(100);
    Serial.println(analogRead(PIN_ADC_VDUT));
    Serial.println(analogRead(PIN_ADC_IDUT)); */

  //Serial.println("--SI--");
  temp = (((unsigned long)nv_iref / ADC_WINDOW_AVG_WEIGHT) * ADC_VREF_MV * ADC_VIREF_ATTENUATION) / 1023;
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}

byte dac_get_state() {
  return digitalRead(PIN_EN_VIN_FET);
}

void dac_on() {
  digitalWrite(PIN_EN_VIN_FET, HIGH);
  en_status = true;
}

void dac_off() {
  digitalWrite(PIN_EN_VIN_FET, LOW);
  en_status = false;
}

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  // setup output pins
  pinMode(PIN_DAC_LSB, OUTPUT);
  pinMode(PIN_DAC_MSB, OUTPUT);
  pinMode(PIN_PS_PWM, OUTPUT);
  pinMode(PIN_EN_VIN_FET, OUTPUT);
  pinMode(PIN_LED_GRN, OUTPUT);
  pinMode(PIN_LED_RED_13, OUTPUT);

  digitalWrite(PIN_EN_VIN_FET, LOW); // make sure EL is not enabled.

  // turn on pull-ups on switch input pins
  digitalWrite(PIN_SW_S2, HIGH);
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  TCCR2B = (1 << CS20); // ps = 1, yielding 31.25kHz

  // set duty cycle to about 50%
  analogWrite(PIN_PS_PWM, 128);

}

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  display.setCursor(0, 0);


  //adc_viref_mv = analogRead(PIN_ADC_V_IREF);
  //adc_idut_ma = analogRead(PIN_ADC_IDUT);
  //adc_vdut_mv = analogRead(PIN_ADC_VDUT);


  static unsigned int i = 0;
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
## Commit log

2017-12-29 Upload previous work
2017-12-29 Uploading more old files

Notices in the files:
parts and their libraries:
SparkFun-DiscreteSemi: Licensing: Creative Commons ShareAlike 4.0 International - https://creativecommons.org/licenses/by-sa/4.0
